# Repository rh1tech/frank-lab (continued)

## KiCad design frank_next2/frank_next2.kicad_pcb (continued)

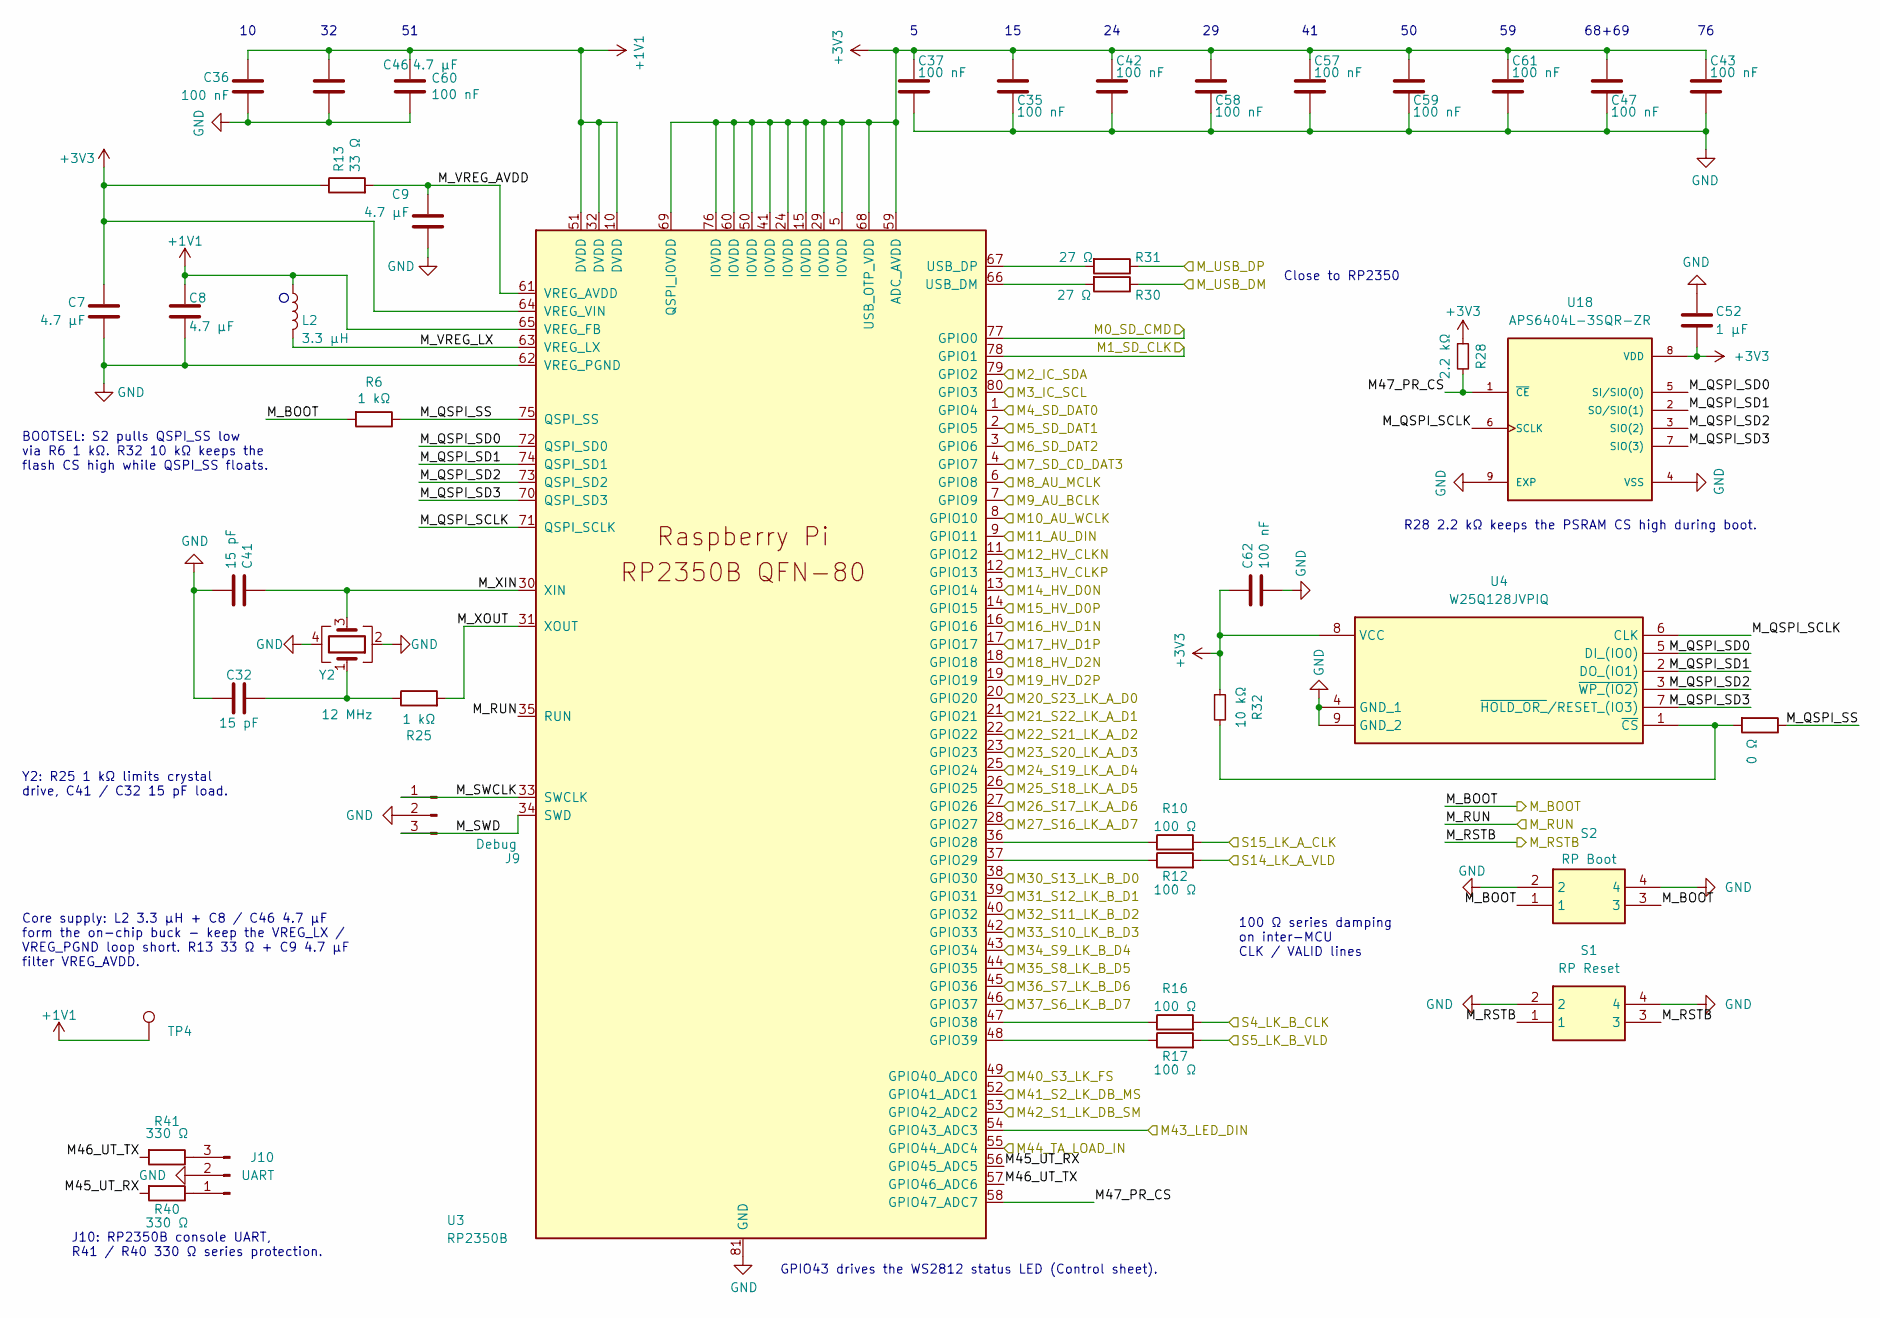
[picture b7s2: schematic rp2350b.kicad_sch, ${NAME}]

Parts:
C7, C8: 4.7 µF 25 V; C_0603_1608Metric_small_pads; LCSC C5360844
C9: 4.7 µF 25 V; C_0603_1608Metric; LCSC C5360844
C32, C41: 15 pF 50 V; C_0603_1608Metric; LCSC C1644
C35, C36, C37, C42, C43, C47, C57, C58, C59, C60, C61: 100 nF 50 V; C_0603_1608Metric_small_pads_Via; LCSC C14663
C46: 4.7 µF 25 V; C_0603_1608Metric_small_pads_Via; LCSC C5360844
C52: 1 µF 50 V; C_0603_1608Metric; LCSC C5199872
C62: 100 nF 50 V; C_0603_1608Metric_small_pads_Via_GND; LCSC C14663
J9: Debug; JST_SH_1x03_P1.00mm_Vertical; LCSC C160389
J10: UART; JST_SH_1x03_P1.00mm_Vertical; LCSC C160389
L2: 3.3 µH; L_AOTA-B201610_2.0x1.6mm; LCSC C42411119
R6, R25: 1 kΩ; R_0603_1608Metric; LCSC C21190
R10, R12, R16, R17: 100 Ω; R_0603_1608Metric; LCSC C22775
R11: 0 Ω; R_0603_1608Metric; LCSC C21189
R13: 33 Ω; R_0603_1608Metric_small_pads; LCSC C23140
R28: 2.2 kΩ; R_0603_1608Metric; LCSC C4190
R30, R31: 27 Ω; R_0603_1608Metric; LCSC C25190
R32: 10 kΩ; R_0603_1608Metric_small_pads_Via; LCSC C2906982
R40, R41: 330 Ω; R_0603_1608Metric; LCSC C23138
S1: RP Reset; Button_SMD_3x4x2mm; Mouser Part Number 611-KMR221G-LFS; LCSC C55200587
S2: RP Boot; Button_SMD_3x4x2mm; Mouser Part Number 611-KMR221G-LFS; LCSC C55200587
TP4: +1V1; TestPoint_Pad_D1.0mm
U3: RP2350B; RP2350-QFN-80_10x10_P0.4mm; LCSC C42415655
U4: W25Q128JVPIQ; WSON-8-1EP_6x5mm_P1.27mm_EP3.45x4.35mm; Mouser Part Number 454-W25Q128JVPIQ; LCSC C190862
U18: APS6404L-3SQR-ZR; PSON50P200X300X50-9N; PARTREV 2.3; LCSC C3040877
Y2: 12 MHz; Crystal_SMD_3225-4Pin_3.2x2.5mm; LCSC C20625731

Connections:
+1V1: C8.1, C36.1, C46.1, C60.1, L2.1, TP4.1 (1_1), U3.10 (DVDD), U3.32 (DVDD), U3.51 (DVDD), U3.65 (VREG_FB)
+3V3: C7.1, C35.1, C37.1, C42.1, C43.1, C47.1, C52.1, C57.1, C58.1, C59.1, C61.1, C62.1, R13.1, R28.1, R32.1, U3.5 (IOVDD), U3.15 (IOVDD), U3.24 (IOVDD), U3.29 (IOVDD), U3.41 (IOVDD), U3.50 (IOVDD), U3.59 (ADC_AVDD), U3.60 (IOVDD), U3.64 (VREG_VIN), U3.68 (USB_OTP_VDD), U3.69 (QSPI_IOVDD), U3.76 (IOVDD), U4.8 (VCC), U18.8 (VDD); also elsewhere on the board
/M0_SD_CMD: U3.77 (GPIO0); also elsewhere on the board
/M1_SD_CLK: U3.78 (GPIO1); also elsewhere on the board
/M2_IC_SDA: U3.79 (GPIO2); also elsewhere on the board
/M3_IC_SCL: U3.80 (GPIO3); also elsewhere on the board
/M4_SD_DAT0: U3.1 (GPIO4); also elsewhere on the board
/M5_SD_DAT1: U3.2 (GPIO5); also elsewhere on the board
/M6_SD_DAT2: U3.3 (GPIO6); also elsewhere on the board
/M7_SD_CD_DAT3: U3.4 (GPIO7); also elsewhere on the board
/M8_AU_MCLK: U3.6 (GPIO8); also elsewhere on the board
/M9_AU_BCLK: U3.7 (GPIO9); also elsewhere on the board
/M10_AU_WCLK: U3.8 (GPIO10); also elsewhere on the board
/M11_AU_DIN: U3.9 (GPIO11); also elsewhere on the board
/M12_HV_CLKN: U3.11 (GPIO12); also elsewhere on the board
/M13_HV_CLKP: U3.12 (GPIO13); also elsewhere on the board
/M14_HV_D0N: U3.13 (GPIO14); also elsewhere on the board
/M15_HV_D0P: U3.14 (GPIO15); also elsewhere on the board
/M16_HV_D1N: U3.16 (GPIO16); also elsewhere on the board
/M17_HV_D1P: U3.17 (GPIO17); also elsewhere on the board
/M18_HV_D2N: U3.18 (GPIO18); also elsewhere on the board
/M19_HV_D2P: U3.19 (GPIO19); also elsewhere on the board
/M20_S23_LK_A_D0: U3.20 (GPIO20); also elsewhere on the board
/M21_S22_LK_A_D1: U3.21 (GPIO21); also elsewhere on the board
/M22_S21_LK_A_D2: U3.22 (GPIO22); also elsewhere on the board
/M23_S20_LK_A_D3: U3.23 (GPIO23); also elsewhere on the board
/M24_S19_LK_A_D4: U3.25 (GPIO24); also elsewhere on the board
/M25_S18_LK_A_D5: U3.26 (GPIO25); also elsewhere on the board
/M26_S17_LK_A_D6: U3.27 (GPIO26); also elsewhere on the board
/M27_S16_LK_A_D7: U3.28 (GPIO27); also elsewhere on the board
/M30_S13_LK_B_D0: U3.38 (GPIO30); also elsewhere on the board
/M31_S12_LK_B_D1: U3.39 (GPIO31); also elsewhere on the board
/M32_S11_LK_B_D2: U3.40 (GPIO32); also elsewhere on the board
/M33_S10_LK_B_D3: U3.42 (GPIO33); also elsewhere on the board
/M34_S9_LK_B_D4: U3.43 (GPIO34); also elsewhere on the board
/M35_S8_LK_B_D5: U3.44 (GPIO35); also elsewhere on the board
/M36_S7_LK_B_D6: U3.45 (GPIO36); also elsewhere on the board
/M37_S6_LK_B_D7: U3.46 (GPIO37); also elsewhere on the board
/M40_S3_LK_FS: U3.49 (GPIO40_ADC0); also elsewhere on the board
/M41_S2_LK_DB_MS: U3.52 (GPIO41_ADC1); also elsewhere on the board
/M42_S1_LK_DB_SM: U3.53 (GPIO42_ADC2); also elsewhere on the board
/M43_LED_DIN: U3.54 (GPIO43_ADC3); also elsewhere on the board
/M_BOOT: R6.2, S2.1, S2.3; also elsewhere on the board
/M_RSTB: S1.1, S1.3; also elsewhere on the board
/M_RUN: U3.35 (RUN); also elsewhere on the board
/RP2350B/M44_TA_LOAD_IN: U3.55 (GPIO44_ADC4); also elsewhere on the board
/RP2350B/M45_UT_RX: R40.2, U3.56 (GPIO45_ADC5)
/RP2350B/M46_UT_TX: R41.2, U3.57 (GPIO46_ADC6)
/RP2350B/M47_PR_CS: R28.2, U3.58 (GPIO47_ADC7), U18.1 (~CE)
/RP2350B/M_QSPI_SCLK: U3.71 (QSPI_SCLK), U4.6 (CLK), U18.6 (SCLK)
/RP2350B/M_QSPI_SD0: U3.72 (QSPI_SD0), U4.5 (DI_(IO0)), U18.5 (SI/SIO(0))
/RP2350B/M_QSPI_SD1: U3.74 (QSPI_SD1), U4.2 (DO_(IO1)), U18.2 (SO/SIO(1))
/RP2350B/M_QSPI_SD2: U3.73 (QSPI_SD2), U4.3 (~WP_(IO2)), U18.3 (SIO(2))
/RP2350B/M_QSPI_SD3: U3.70 (QSPI_SD3), U4.7 (~HOLD_OR_/RESET_(IO3)), U18.7 (SIO(3))
/RP2350B/M_QSPI_SS: R6.1, R11.1, U3.75 (QSPI_SS)
/RP2350B/M_SWCLK: J9.1, U3.33 (SWCLK)
/RP2350B/M_SWD: J9.3, U3.34 (SWD)
/RP2350B/M_USB_DM: R30.1; also elsewhere on the board
/RP2350B/M_USB_DP: R31.1; also elsewhere on the board
/RP2350B/M_VREG_AVDD: C9.1, R13.2, U3.61 (VREG_AVDD)
/RP2350B/M_VREG_LX: L2.2, U3.63 (VREG_LX)
/RP2350B/M_XIN: C41.1, U3.30 (XIN), Y2.3
/RP2350B/M_XOUT: R25.2, U3.31 (XOUT)
/S4_LK_B_CLK: R16.2; also elsewhere on the board
/S5_LK_B_VLD: R17.2; also elsewhere on the board
/S14_LK_A_VLD: R12.2; also elsewhere on the board
/S15_LK_A_CLK: R10.2; also elsewhere on the board
GND: C7.2, C8.2, C9.2, C32.2, C35.2, C36.2, C37.2, C41.2, C42.2, C43.2, C46.2, C47.2, C52.2, C57.2, C58.2, C59.2, C60.2, C61.2, C62.2, J9.2, J10.2, S1.2, S1.4, S2.2, S2.4, U3.62 (VREG_PGND), U3.81 (GND), U4.4 (GND_1), U4.9 (GND_2), U18.4 (VSS), U18.9 (EXP), Y2.2, Y2.4; also elsewhere on the board
unnamed: C32.1, R25.1, Y2.1
unnamed: J10.1, R40.1
unnamed: J10.3, R41.1
unnamed: R10.1, U3.36 (GPIO28)
unnamed: R12.1, U3.37 (GPIO29)
unnamed: R16.1, U3.47 (GPIO38)
unnamed: R17.1, U3.48 (GPIO39)
unnamed: R30.2, U3.66 (USB_DM)
unnamed: R31.2, U3.67 (USB_DP)
unnamed: R11.2, R32.2, U4.1 (~CS)

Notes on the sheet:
J10: RP2350B console UART, R41 / R40 330 Ω series protection.
BOOTSEL: S2 pulls QSPI_SS low via R6 1 kΩ. R32 10 kΩ keeps the flash CS high while QSPI_SS floats.
100 Ω series damping on inter-MCU CLK / VALID lines
Core supply: L2 3.3 µH + C8 / C46 4.7 µF form the on-chip buck - keep the VREG_LX / VREG_PGND loop short. R13 33 Ω + C9 4.7 µF filter VREG_AVDD.
GPIO43 drives the WS2812 status LED (Control sheet).
Close to RP2350
R28 2.2 kΩ keeps the PSRAM CS high during boot.
68+69
Y2: R25 1 kΩ limits crystal drive, C41 / C32 15 pF load.

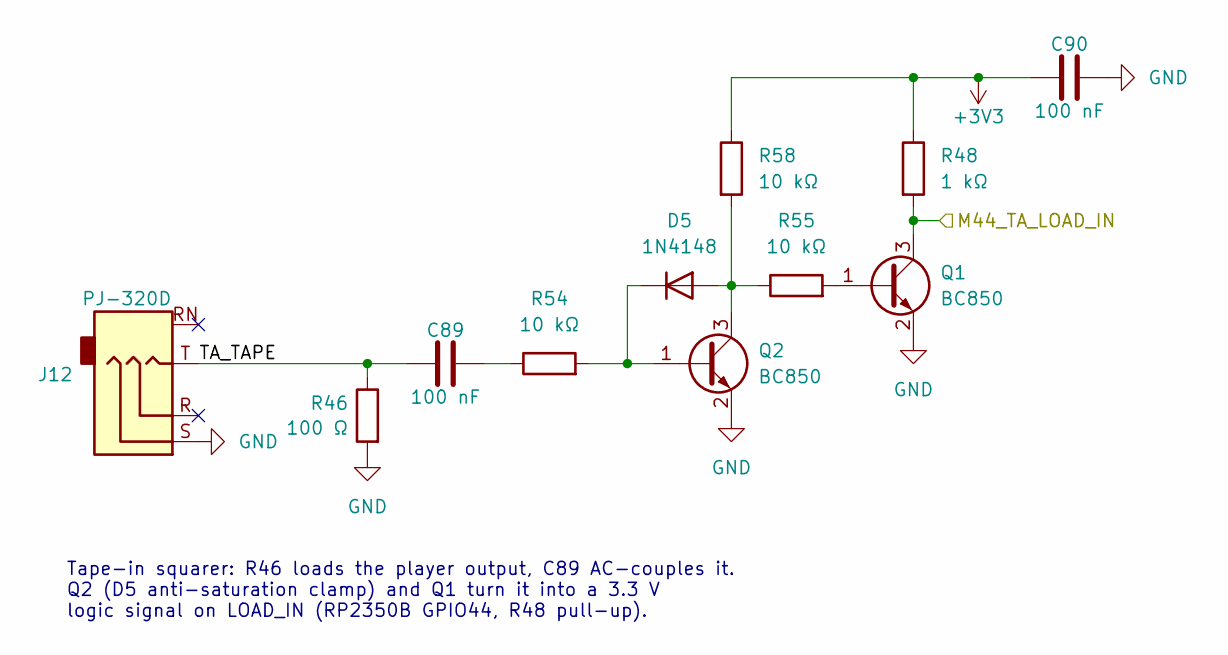
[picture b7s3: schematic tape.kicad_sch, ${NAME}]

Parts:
C89: 100 nF 50 V; C_0603_1608Metric; LCSC C14663
C90: 100 nF 50 V; C_0603_1608Metric_small_pads_Via_GND; LCSC C14663
D5: 1N4148; D_SOD-323; LCSC C2128
J12: PJ-320D; AudioJack_3.5mm_PJ320D_TapeIn; LCSC C431535
Q1, Q2: BC850; SOT-23; LCSC C503377
R46: 100 Ω; R_0603_1608Metric; LCSC C22775
R48: 1 kΩ; R_0603_1608Metric_small_pads_Via; LCSC C21190
R54, R55: 10 kΩ; R_0603_1608Metric; LCSC C2906982
R58: 10 kΩ; R_0603_1608Metric_small_pads_Via; LCSC C2906982

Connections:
+3V3: C90.1, R48.1, R58.1; also elsewhere on the board
/RP2350B/M44_TA_LOAD_IN: Q1.3 (C), R48.2; also elsewhere on the board
/Tape/TA_TAPE: C89.1, J12.T, R46.1
GND: C90.2, J12.S, Q1.2 (E), Q2.2 (E), R46.2; also elsewhere on the board
unnamed: C89.2, R54.1
unnamed: D5.2 (A), Q2.3 (C), R55.1, R58.2
unnamed: D5.1 (K), Q2.1 (B), R54.2
unnamed: Q1.1 (B), R55.2

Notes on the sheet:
Tape-in squarer: R46 loads the player output, C89 AC-couples it. Q2 (D5 anti-saturation clamp) and Q1 turn it into a 3.3 V logic signal on LOAD_IN (RP2350B GPIO44, R48 pull-up).

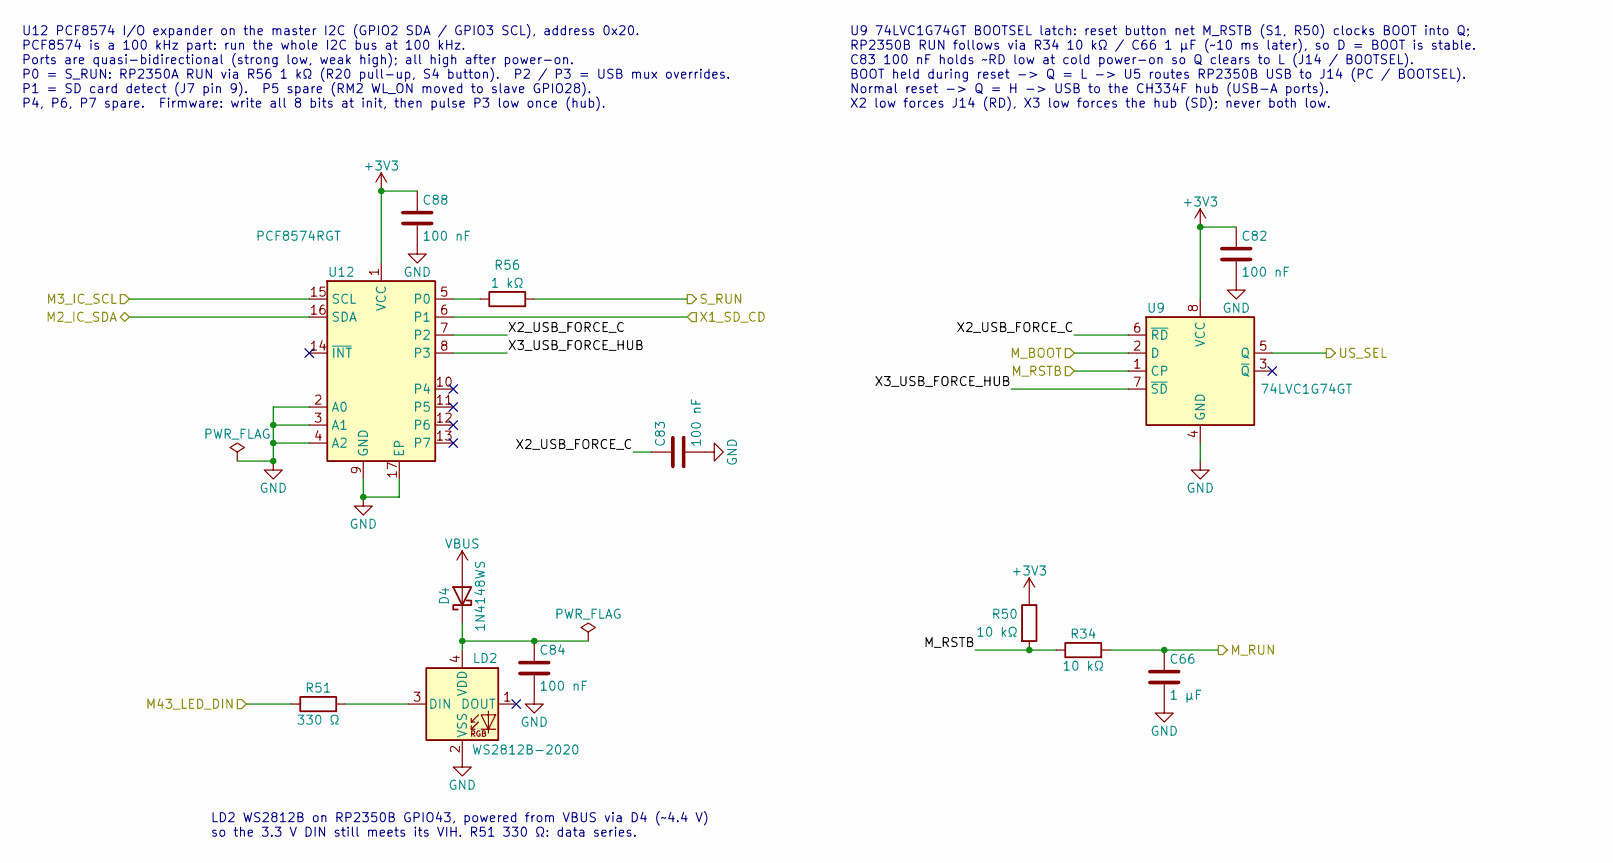
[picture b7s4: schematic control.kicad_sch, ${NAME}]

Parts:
C66: 1 µF 50 V; C_0603_1608Metric; LCSC C5199872
C82, C88: 100 nF 50 V; C_0603_1608Metric_small_pads_Via_GND; LCSC C14663
C83, C84: 100 nF 50 V; C_0603_1608Metric; LCSC C14663
D4: 1N4148WS; D_SOD-323; LCSC C2128
LD2: WS2812B-2020; LED_WS2812B-2020_PLCC4_2.0x2.0mm; LCSC C965555
R34: 10 kΩ; R_0603_1608Metric; LCSC C2906982
R50: 10 kΩ; R_0603_1608Metric_small_pads_Via; LCSC C2906982
R51: 330 Ω; R_0603_1608Metric; LCSC C23138
R56: 1 kΩ; R_0603_1608Metric; LCSC C21190
U9: 74LVC1G74GT; Nexperia_XSON-8_SOT833-1_1x1.95mm_P0.5mm; LCSC C548415
U12: PCF8574RGT; VQFN-16-1EP_3x3mm_P0.5mm_EP1.68x1.68mm; LCSC C2652270

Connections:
+3V3: C82.1, C88.1, R50.1, U9.8 (VCC), U12.1 (VCC); also elsewhere on the board
/Control/X2_USB_FORCE_C: C83.1, U9.6 (~RD), U12.7 (P2)
/Control/X3_USB_FORCE_HUB: U9.7 (~SD), U12.8 (P3)
/M2_IC_SDA: U12.16 (SDA); also elsewhere on the board
/M3_IC_SCL: U12.15 (SCL); also elsewhere on the board
/M43_LED_DIN: R51.1; also elsewhere on the board
/M_BOOT: U9.2 (D); also elsewhere on the board
/M_RSTB: R34.1, R50.2, U9.1 (CP); also elsewhere on the board
/M_RUN: C66.1, R34.2; also elsewhere on the board
/S_RUN: R56.2; also elsewhere on the board
/US_SEL: U9.5 (Q); also elsewhere on the board
/X1_SD_CD: U12.6 (P1); also elsewhere on the board
GND: C66.2, C82.2, C83.2, C84.2, C88.2, LD2.2 (VSS), U9.4 (GND), U12.2 (A0), U12.3 (A1), U12.4 (A2), U12.9 (GND), U12.17 (EP); also elsewhere on the board
unnamed: C84.1, D4.1 (K), LD2.4 (VDD)
unnamed: LD2.3 (DIN), R51.2
unnamed: R56.1, U12.5 (P0)
VBUS: D4.2 (A); also elsewhere on the board

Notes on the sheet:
U9 74LVC1G74GT BOOTSEL latch: reset button net M_RSTB (S1, R50) clocks BOOT into Q; RP2350B RUN follows via R34 10 kΩ / C66 1 µF (~10 ms later), so D = BOOT is stable. C83 100 nF holds ~RD low at cold power-on so Q clears to L (J14 / BOOTSEL). BOOT held during reset -> Q = L -> U5 routes RP2350B US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
LD2 WS2812B on RP2350B GPIO43, powered from VBUS via D4 (~4.4 V) so the 3.3 V DIN still meets its VIH. R51 330 Ω: data series.
U12 PCF8574 I/O expander on the master I2C (GPIO2 SDA / GPIO3 SCL), address 0x20. PCF8574 is a 100 kHz part: run the whole I2C bus at 100 kHz. Ports are quasi-bidirectional (strong low, weak high); all high after power-on. P0 = S_RUN: RP2350A RUN via R56 1 kΩ (R20 pull-up, S4 button). P2 / P3 = USB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

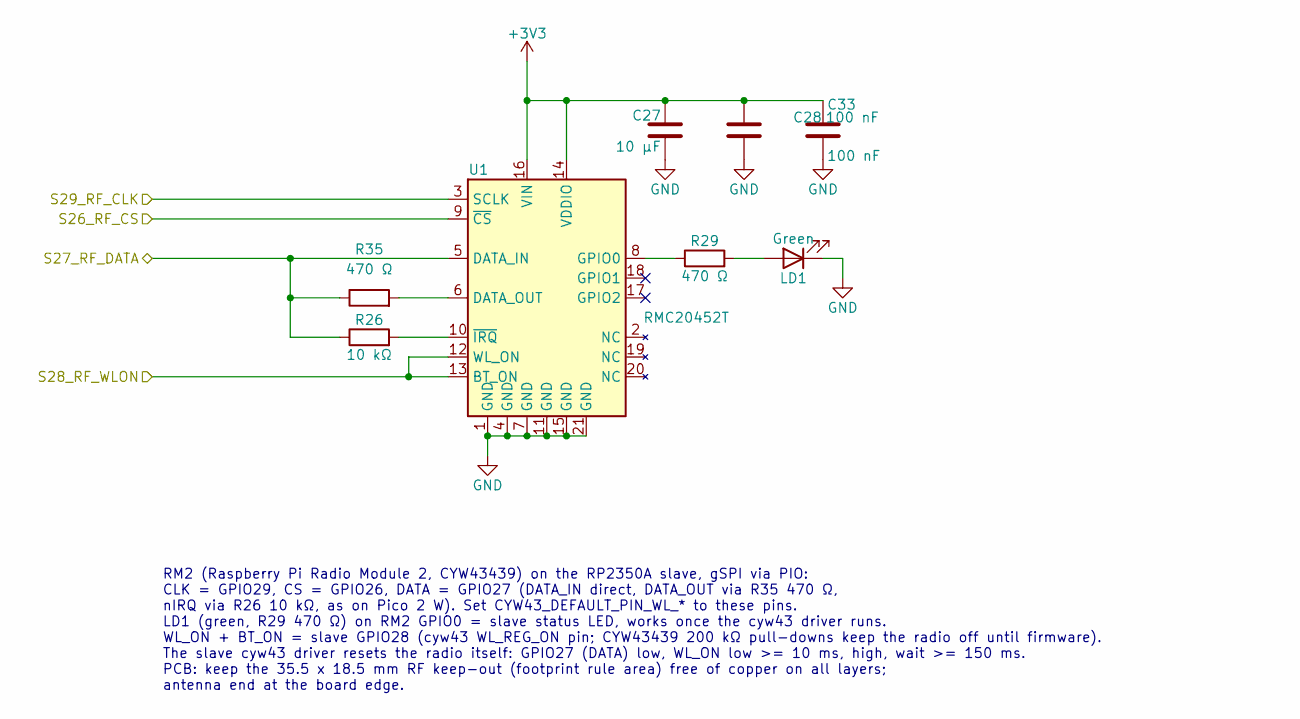
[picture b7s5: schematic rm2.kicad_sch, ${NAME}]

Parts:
C27: 10 µF 25 V; C_0603_1608Metric_small_pads_Via_GND; LCSC C96446
C28, C33: 100 nF 50 V; C_0603_1608Metric_small_pads_Via_GND; LCSC C14663
LD1: Green; LED_0603_1608Metric; LCSC C965804
R26: 10 kΩ; R_0603_1608Metric; LCSC C2906982
R29, R35: 470 Ω; R_0603_1608Metric; LCSC C23179
U1: RMC20452T; RaspberryPi_RM2

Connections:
+3V3: C27.1, C28.1, C33.1, U1.14 (VDDIO), U1.16 (VIN); also elsewhere on the board
/S26_RF_CS: U1.9 (~CS); also elsewhere on the board
/S27_RF_DATA: R26.1, R35.1, U1.5 (DATA_IN); also elsewhere on the board
/S28_RF_WLON: U1.12 (WL_ON), U1.13 (BT_ON); also elsewhere on the board
/S29_RF_CLK: U1.3 (SCLK); also elsewhere on the board
GND: C27.2, C28.2, C33.2, LD1.1 (K), U1.1 (GND), U1.4 (GND), U1.7 (GND), U1.11 (GND), U1.15 (GND), U1.21 (GND); also elsewhere on the board
unnamed: LD1.2 (A), R29.2
unnamed: R35.2, U1.6 (DATA_OUT)
unnamed: R29.1, U1.8 (GPIO0)
unnamed: R26.2, U1.10 (~IRQ)

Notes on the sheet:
RM2 (Raspberry Pi Radio Module 2, CYW43439) on the RP2350A slave, gSPI via PIO: CLK = GPIO29, CS = GPIO26, DATA = GPIO27 (DATA_IN direct, DATA_OUT via R35 470 Ω, nIRQ via R26 10 kΩ, as on Pico 2 W). Set CYW43_DEFAULT_PIN_WL_* to these pins. LD1 (green, R29 470 Ω) on RM2 GPIO0 = slave status LED, wo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

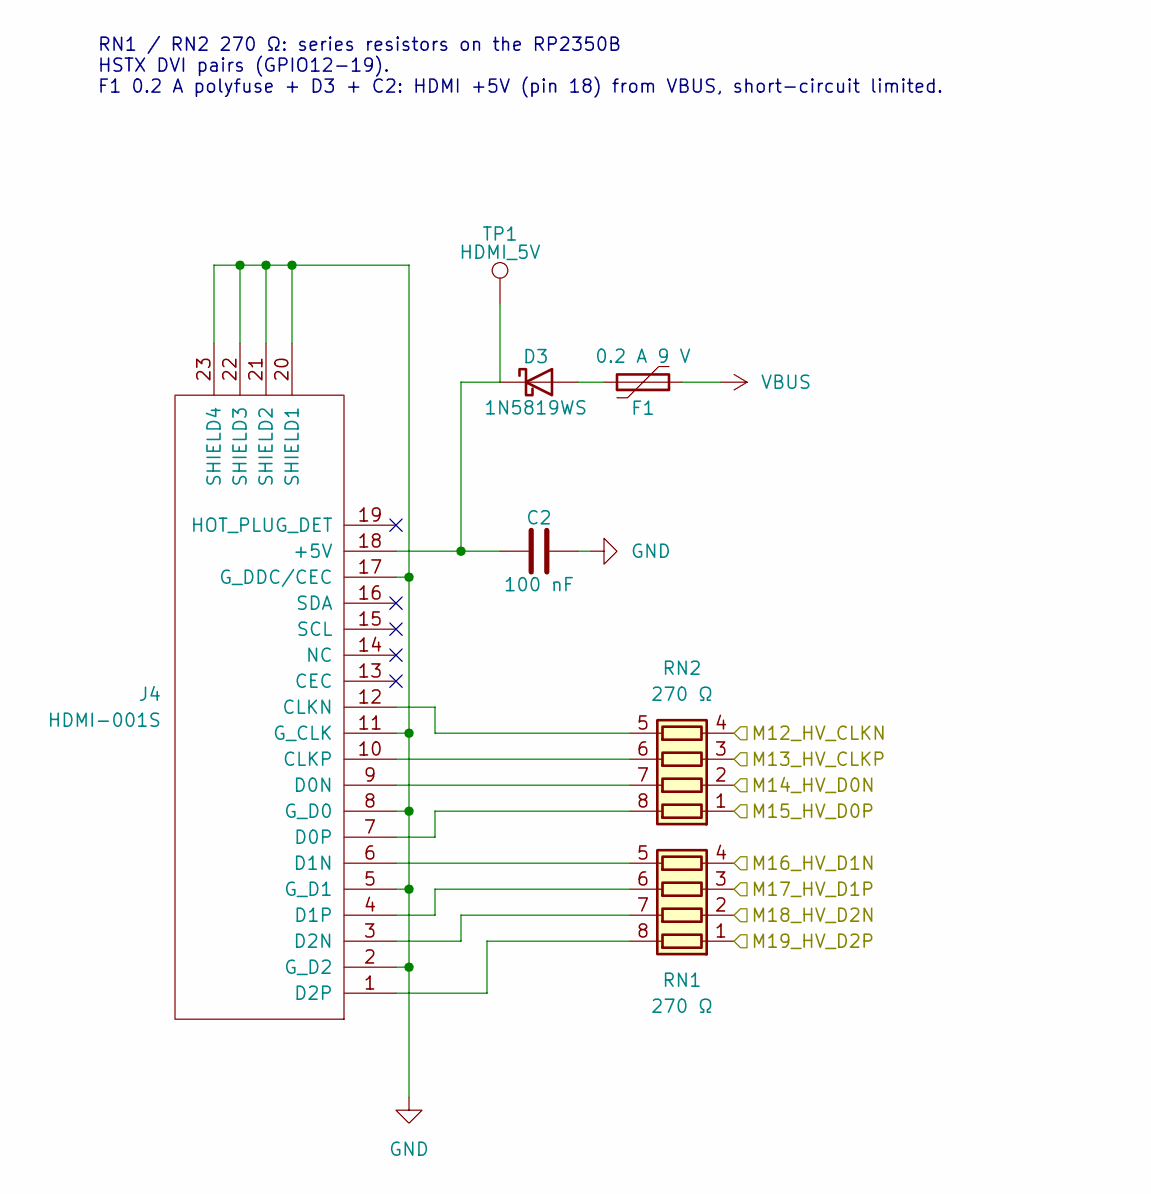
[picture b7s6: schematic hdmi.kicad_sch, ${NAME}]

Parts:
C2: 100 nF 50 V; C_0603_1608Metric; LCSC C14663
D3: 1N5819WS; D_SOD-323; LCSC C191023
F1: 0.2 A 9 V; Fuse_0603_1608Metric; LCSC C20785
J4: HDMI-001S; HDMI_Female; LCSC C720616
RN1, RN2: 270 Ω; R_Array_4x0603; LCSC C1731063
TP1: HDMI_5V; TestPoint_Pad_D1.0mm

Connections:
/M12_HV_CLKN: RN2.4 (R4.1); also elsewhere on the board
/M13_HV_CLKP: RN2.3 (R3.1); also elsewhere on the board
/M14_HV_D0N: RN2.2 (R2.1); also elsewhere on the board
/M15_HV_D0P: RN2.1 (R1.1); also elsewhere on the board
/M16_HV_D1N: RN1.4 (R4.1); also elsewhere on the board
/M17_HV_D1P: RN1.3 (R3.1); also elsewhere on the board
/M18_HV_D2N: RN1.2 (R2.1); also elsewhere on the board
/M19_HV_D2P: RN1.1 (R1.1); also elsewhere on the board
GND: C2.2, J4.2 (G_D2), J4.5 (G_D1), J4.8 (G_D0), J4.11 (G_CLK), J4.17 (G_DDC/CEC), J4.20 (SHIELD1), J4.21 (SHIELD2), J4.22 (SHIELD3), J4.23 (SHIELD4); also elsewhere on the board
unnamed: D3.2 (A), F1.1
unnamed: C2.1, D3.1 (K), J4.18 (+5V), TP1.1 (1_1)
unnamed: J4.12 (CLKN), RN2.5 (R4.2)
unnamed: J4.10 (CLKP), RN2.6 (R3.2)
unnamed: J4.9 (D0N), RN2.7 (R2.2)
unnamed: J4.7 (D0P), RN2.8 (R1.2)
unnamed: J4.6 (D1N), RN1.5 (R4.2)
unnamed: J4.4 (D1P), RN1.6 (R3.2)
unnamed: J4.3 (D2N), RN1.7 (R2.2)
unnamed: J4.1 (D2P), RN1.8 (R1.2)
VBUS: F1.2; also elsewhere on the board

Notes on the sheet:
RN1 / RN2 270 Ω: series resistors on the RP2350B HSTX DVI pairs (GPIO12-19). F1 0.2 A polyfuse + D3 + C2: HDMI +5V (pin 18) from VBUS, short-circuit limited.

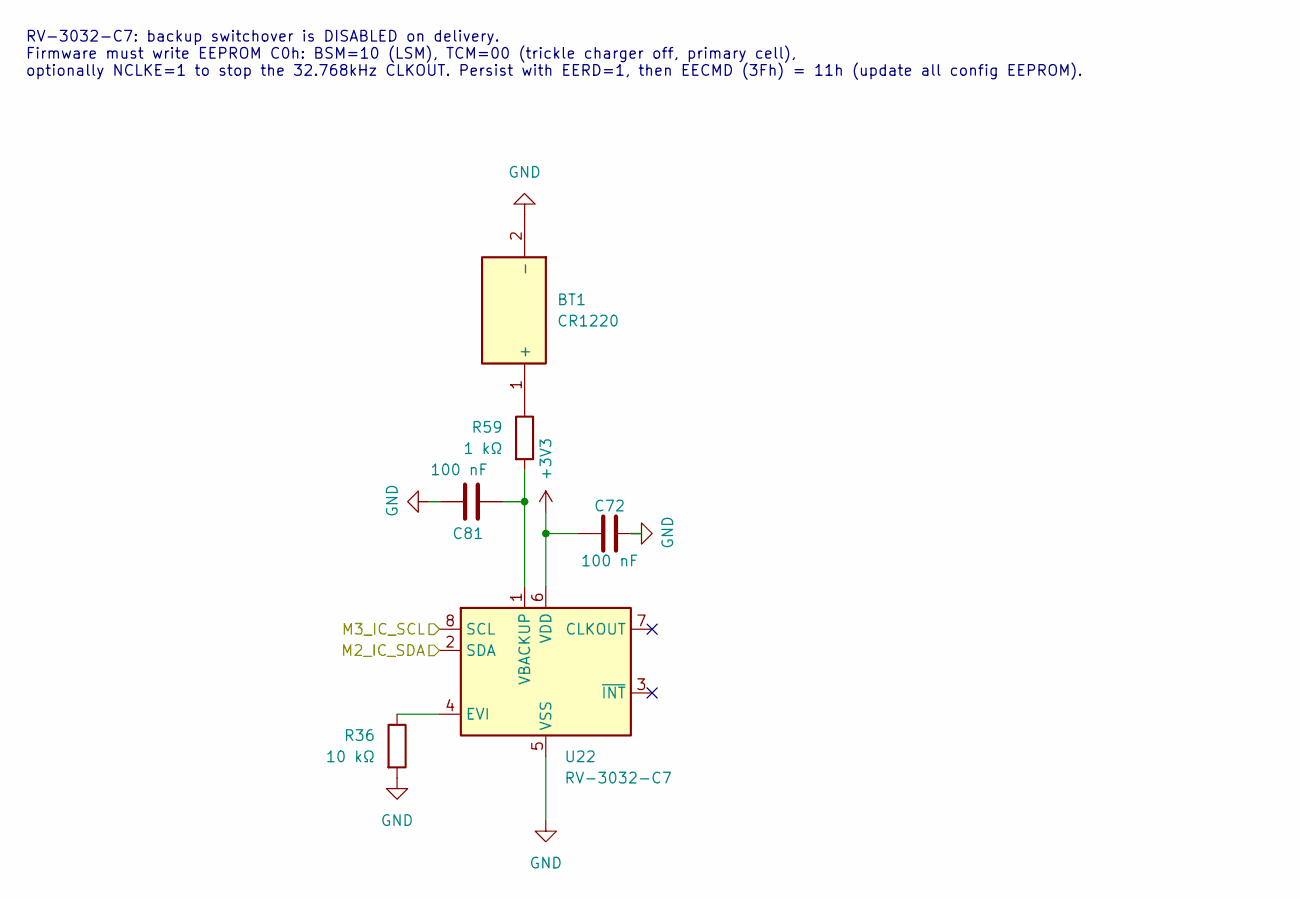
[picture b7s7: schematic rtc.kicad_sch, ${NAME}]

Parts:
BT1: CR1220; Battery_CR1220_MYOUNG_BS-12-B3AA003; Manufacturer_Part_Number BS-12-B3AA003; LCSC C964723
C72: 100 nF 50 V; C_0603_1608Metric_small_pads_Via_GND; LCSC C14663
C81: 100 nF 50 V; C_0603_1608Metric; LCSC C14663
R36: 10 kΩ; R_0603_1608Metric; LCSC C2906982
R59: 1 kΩ; R_0603_1608Metric; LCSC C21190
U22: RV-3032-C7; LCSC C5127802

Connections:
+3V3: C72.1, U22.6 (VDD); also elsewhere on the board
/M2_IC_SDA: U22.2 (SDA); also elsewhere on the board
/M3_IC_SCL: U22.8 (SCL); also elsewhere on the board
GND: BT1.2 (-), C72.2, C81.1, R36.2, U22.5 (VSS); also elsewhere on the board
unnamed: BT1.1 (+), R59.1
unnamed: R36.1, U22.4 (EVI)
unnamed: C81.2, R59.2, U22.1 (VBACKUP)

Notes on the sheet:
RV-3032-C7: backup switchover is DISABLED on delivery. Firmware must write EEPROM C0h: BSM=10 (LSM), TCM=00 (trickle charger off, primary cell), optionally NCLKE=1 to stop the 32.768kHz CLKOUT. Persist with EERD=1, then EECMD (3Fh) = 11h (update all config EEPROM).

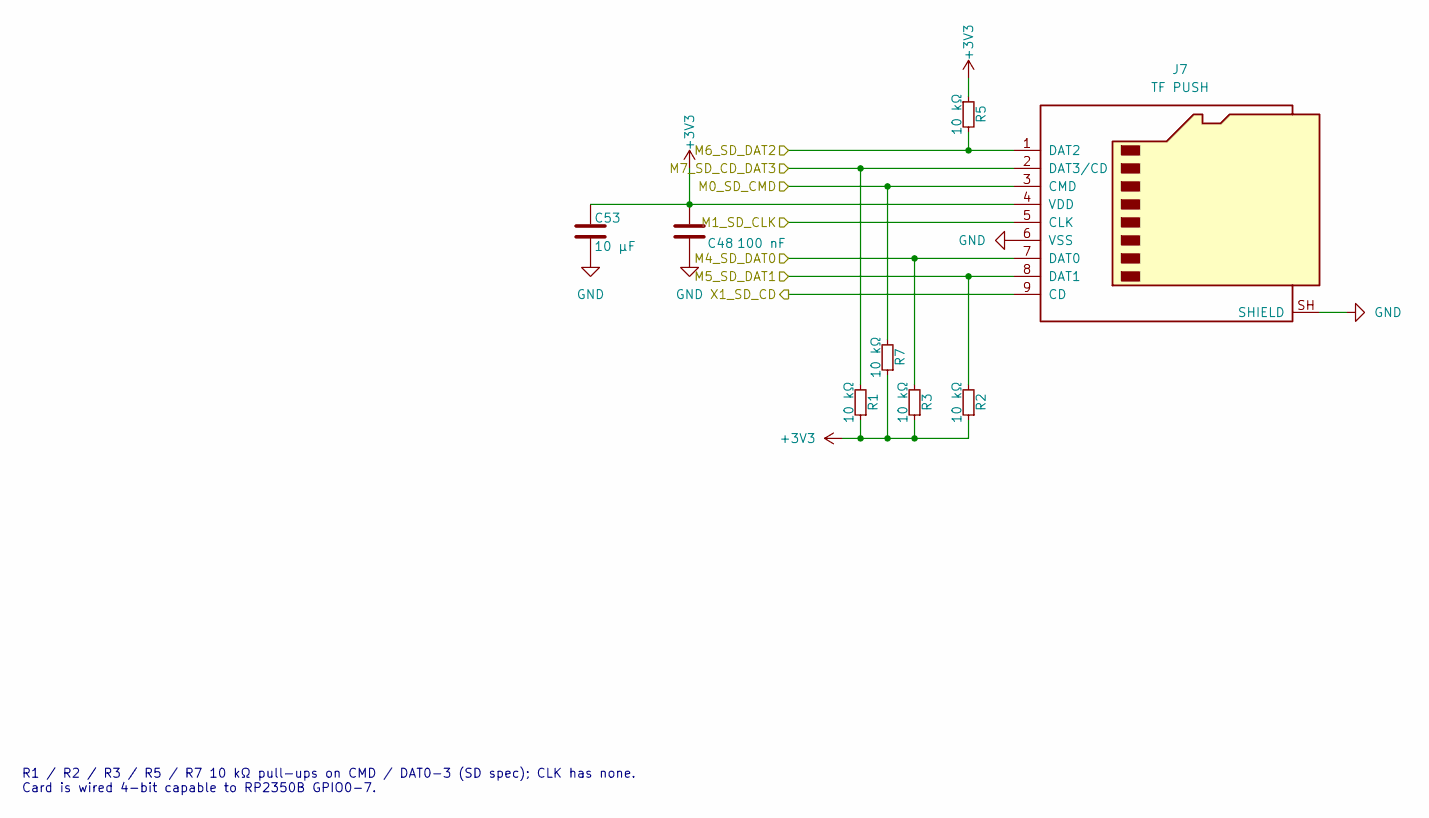
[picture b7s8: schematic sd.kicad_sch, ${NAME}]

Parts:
C48: 100 nF 50 V; C_0603_1608Metric_small_pads_Via_GND; LCSC C14663
C53: 10 µF 25 V; C_0603_1608Metric_small_pads_Via_GND; LCSC C96446
J7: TF PUSH; MicroSD_SMD_Long; LCSC C393941
R1, R2, R3, R5, R7: 10 kΩ; R_0603_1608Metric_small_pads_Via; LCSC C2906982

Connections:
+3V3: C48.1, C53.1, J7.4 (VDD), R1.1, R2.1, R3.1, R5.1, R7.1; also elsewhere on the board
/M0_SD_CMD: J7.3 (CMD), R7.2; also elsewhere on the board
/M1_SD_CLK: J7.5 (CLK); also elsewhere on the board
/M4_SD_DAT0: J7.7 (DAT0), R3.2; also elsewhere on the board
/M5_SD_DAT1: J7.8 (DAT1), R2.2; also elsewhere on the board
/M6_SD_DAT2: J7.1 (DAT2), R5.2; also elsewhere on the board
/M7_SD_CD_DAT3: J7.2 (DAT3/CD), R1.2; also elsewhere on the board
/X1_SD_CD: J7.9 (CD); also elsewhere on the board
GND: C48.2, C53.2, J7.6 (VSS), J7.SH (SHIELD); also elsewhere on the board

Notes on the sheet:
R1 / R2 / R3 / R5 / R7 10 kΩ pull-ups on CMD / DAT0-3 (SD spec); CLK has none. Card is wired 4-bit capable to RP2350B GPIO0-7.

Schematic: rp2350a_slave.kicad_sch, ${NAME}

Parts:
C4: 4.7 µF 25 V; C_0603_1608Metric; LCSC C5360844
C5, C6: 4.7 µF 25 V; C_0603_1608Metric_small_pads; LCSC C5360844
C34, C38, C39, C40, C44, C50, C54, C55, C56: 100 nF 50 V; C_0603_1608Metric_small_pads_Via; LCSC C14663
C45: 4.7 µF 25 V; C_0603_1608Metric_small_pads_Via; LCSC C5360844
C49: 100 nF 50 V; C_0603_1608Metric; LCSC C14663
C51, C65: 15 pF 50 V; C_0603_1608Metric; LCSC C1644
C63: 1 µF 50 V; C_0603_1608Metric_small_pads_Via_GND; LCSC C5199872
J5: Debug; JST_SH_1x03_P1.00mm_Vertical; LCSC C160389
J6: UART; JST_SH_1x03_P1.00mm_Vertical; LCSC C160389
L1: 3.3 µH; L_AOTA-B201610_2.0x1.6mm; LCSC C42411119
R4: 33 Ω; R_0603_1608Metric_small_pads; LCSC C23140
R8, R9: 27 Ω; R_0603_1608Metric; LCSC C25190
R22, R27: 1 kΩ; R_0603_1608Metric; LCSC C21190
R23: 10 kΩ; R_0603_1608Metric; LCSC C2906982
R24: 0 Ω; R_0603_1608Metric; LCSC C21189
R33: 2.2 kΩ; R_0603_1608Metric_small_pads_Via; LCSC C4190
S3: RP Boot; Button_SMD_3x4x2mm; Mouser Part Number 611-KMR221G-LFS; LCSC C55200587
S4: RP Reset; Button_SMD_3x4x2mm; Mouser Part Number 611-KMR221G-LFS; LCSC C55200587
TP3: +1V1_A; TestPoint_Pad_D1.0mm
U2: RP2350; QFN-60-1EP_7x7mm_P0.4mm_EP3.4x3.4mm; LCSC C42411118
U19: W25Q128JVPIQ; WSON-8-1EP_6x5mm_P1.27mm_EP3.45x4.35mm; Mouser Part Number 454-W25Q128JVPIQ; LCSC C190862
U20: APS6404L-3SQR-ZR; PSON50P200X300X50-9N; PARTREV 2.3; LCSC C3040877
Y3: 12 MHz; Crystal_SMD_3225-4Pin_3.2x2.5mm; LCSC C20625731

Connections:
+1V1_A: C5.1, C39.1, C45.1, C55.1, L1.1, TP3.1 (1_1), U2.6 (DVDD), U2.23 (DVDD), U2.39 (DVDD), U2.50 (VREG_FB)
+3V3: C6.1, C34.1, C38.1, C40.1, C44.1, C49.1, C50.1, C54.1, C56.1, C63.1, R4.1, R23.1, R33.1, U2.1 (IOVDD), U2.11 (IOVDD), U2.20 (IOVDD), U2.30 (IOVDD), U2.38 (IOVDD), U2.44 (ADC_AVDD), U2.45 (IOVDD), U2.49 (VREG_VIN), U2.53 (USB_OTP_VDD), U2.54 (QSPI_IOVDD), U19.8 (VCC), U20.8 (VDD); also elsewhere on the board
/M20_S23_LK_A_D0: U2.35 (GPIO23); also elsewhere on the board
/M21_S22_LK_A_D1: U2.34 (GPIO22); also elsewhere on the board
/M22_S21_LK_A_D2: U2.33 (GPIO21); also elsewhere on the board
/M23_S20_LK_A_D3: U2.32 (GPIO20); also elsewhere on the board
/M24_S19_LK_A_D4: U2.31 (GPIO19); also elsewhere on the board
/M25_S18_LK_A_D5: U2.29 (GPIO18); also elsewhere on the board
/M26_S17_LK_A_D6: U2.28 (GPIO17); also elsewhere on the board
/M27_S16_LK_A_D7: U2.27 (GPIO16); also elsewhere on the board
/M30_S13_LK_B_D0: U2.17 (GPIO13); also elsewhere on the board
/M31_S12_LK_B_D1: U2.16 (GPIO12); also elsewhere on the board
/M32_S11_LK_B_D2: U2.15 (GPIO11); also elsewhere on the board
/M33_S10_LK_B_D3: U2.14 (GPIO10); also elsewhere on the board
/M34_S9_LK_B_D4: U2.13 (GPIO9); also elsewhere on the board
/M35_S8_LK_B_D5: U2.12 (GPIO8); also elsewhere on the board
/M36_S7_LK_B_D6: U2.10 (GPIO7); also elsewhere on the board
/M37_S6_LK_B_D7: U2.9 (GPIO6); also elsewhere on the board
/M40_S3_LK_FS: U2.5 (GPIO3); also elsewhere on the board
/M41_S2_LK_DB_MS: U2.4 (GPIO2); also elsewhere on the board
/M42_S1_LK_DB_SM: U2.3 (GPIO1); also elsewhere on the board
/RP2350A/S0_PR_CS: R33.2, U2.2 (GPIO0), U20.1 (~CE)
/RP2350A/S24_UT_TX: J6.3, U2.36 (GPIO24)
/RP2350A/S25_UT_RX: J6.1, U2.37 (GPIO25)
/RP2350A/S_BOOT: R22.2, S3.1, S3.3
/RP2350A/S_QSPI_SCLK: U2.56 (QSPI_SCLK), U19.6 (CLK), U20.6 (SCLK)
/RP2350A/S_QSPI_SD0: U2.57 (QSPI_SD0), U19.5 (DI_(IO0)), U20.5 (SI/SIO(0))
/RP2350A/S_QSPI_SD1: U2.59 (QSPI_SD1), U19.2 (DO_(IO1)), U20.2 (SO/SIO(1))
/RP2350A/S_QSPI_SD2: U2.58 (QSPI_SD2), U19.3 (~WP_(IO2)), U20.3 (SIO(2))
/RP2350A/S_QSPI_SD3: U2.55 (QSPI_SD3), U19.7 (~HOLD_OR_/RESET_(IO3)), U20.7 (SIO(3))
/RP2350A/S_QSPI_SS: R22.1, R24.1, U2.60 (QSPI_SS)
/RP2350A/S_SWCLK: J5.1, U2.24 (SWCLK)
/RP2350A/S_SWD: J5.3, U2.25 (SWD)
/RP2350A/S_VREG_AVDD: C4.1, R4.2, U2.46 (VREG_AVDD)
/RP2350A/S_VREG_LX: L1.2, U2.48 (VREG_LX)
/RP2350A/S_XIN: C51.1, U2.21 (XIN), Y3.3
/RP2350A/S_XOUT: R27.2, U2.22 (XOUT)
/S4_LK_B_CLK: U2.7 (GPIO4); also elsewhere on the board
/S5_LK_B_VLD: U2.8 (GPIO5); also elsewhere on the board
/S14_LK_A_VLD: U2.18 (GPIO14); also elsewhere on the board
/S15_LK_A_CLK: U2.19 (GPIO15); also elsewhere on the board
/S26_RF_CS: U2.40 (GPIO26_ADC0); also elsewhere on the board
/S27_RF_DATA: U2.41 (GPIO27_ADC1); also elsewhere on the board
/S28_RF_WLON: U2.42 (GPIO28_ADC2); also elsewhere on the board
/S29_RF_CLK: U2.43 (GPIO29_ADC3); also elsewhere on the board
/S_RUN: S4.1, S4.3, U2.26 (RUN); also elsewhere on the board
/USB/S_USB_DM: R9.1; also elsewhere on the board
/USB/S_USB_DP: R8.1; also elsewhere on the board
GND: C4.2, C5.2, C6.2, C34.2, C38.2, C39.2, C40.2, C44.2, C45.2, C49.2, C50.2, C51.2, C54.2, C55.2, C56.2, C63.2, C65.2, J5.2, J6.2, S3.2, S3.4, S4.2, S4.4, U2.47 (VREG_PGND), U2.61 (GND), U19.4 (GND_1), U19.9 (GND_2), U20.4 (VSS), U20.9 (EXP), Y3.2, Y3.4; also elsewhere on the board
unnamed: C65.1, R27.1, Y3.1
unnamed: R9.2, U2.51 (USB_DM)
unnamed: R8.2, U2.52 (USB_DP)
unnamed: R23.2, R24.2, U19.1 (~CS)

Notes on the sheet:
44+45
Core supply: L1 3.3 µH + C5 / C45 4.7 µF = on-chip buck, keep the loop short. R4 33 Ω + C4 4.7 µF filter VREG_AVDD.
Make sure these are close to RP2350
PSRAM: one APS6404L (U20, 8 MB) on QMI CS1 = GPIO0, R33 2.2 kΩ pull-up. GPIO28 = S28_RF_WLON (RM2 WL_ON + BT_ON).
S3 BOOT: QSPI_SS low via R22 1 kΩ. RUN (S_RUN) = U12 P0 via R56 (Control sheet).
53+54

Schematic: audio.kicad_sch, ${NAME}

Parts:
C11, C67, C70, C71, C75: 100 nF 50 V; C_0603_1608Metric_small_pads_Via_GND; LCSC C14663
C13, C18, C64, C74, C78, C80: 10 µF 25 V; C_0603_1608Metric_small_pads_Via_GND; LCSC C96446
C68: 1 µF 50 V; C_0603_1608Metric_small_pads_Via_GND; LCSC C5199872
C79: 1 µF 50 V; C_0603_1608Metric; LCSC C5199872
C87, C91: 100 µF 10 V; C_1206_3216Metric; LCSC C7432784
J8: Speaker; JST_GH_1x02_P1.25mm; LCSC C114130
J11: PJ-320D; AudioJack_3.5mm_PJ320D_AudioOut; LCSC C431535
L5: 330 Ω@100 MHz 2.5 A; L_0805_2012Metric; LCSC C76819
R14, R15: 4.7 kΩ; R_0603_1608Metric_small_pads_Via; LCSC C23162
R44: 10 kΩ; R_0603_1608Metric_small_pads_Via; LCSC C2906982
TP9: +5V_SPK; TestPoint_Pad_D1.0mm
TP10: +1V8; TestPoint_Pad_D1.0mm
U7: TLV320DAC3100IRHBR; Mouser Part Number 595-V320DAC3100IRHBR; LCSC C179677
U21: XC6206P182MR-G; Mouser Part Number 865-XC6206P182MR-G; LCSC C347373

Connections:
+1V8: C71.1, C80.1, TP10.1 (1_1), U7.3 (DVDD), U21.2 (VOUT)
+3V3: C11.1, C13.1, C18.1, C64.1, C67.1, C68.1, C75.1, R14.1, R15.1, R44.1, U7.2 (IOVDD), U7.17 (AVDD), U7.28 (HPVDD), U21.3 (VIN); also elsewhere on the board
/Audio/+5V_SPK: C70.1, C74.1, C78.1, L5.1, TP9.1 (1_1), U7.21 (SPKVDD_1), U7.24 (SPKVDD_2)
/Audio/AU_SPKM: J8.2, U7.19 (SPKM_1), U7.23 (SPKM_2)
/Audio/AU_SPKP: J8.1, U7.22 (SPKP_1), U7.26 (SPKP_2)
/M2_IC_SDA: R15.2, U7.9 (SDA); also elsewhere on the board
/M3_IC_SCL: R14.2, U7.10 (SCL); also elsewhere on the board
/M8_AU_MCLK: U7.8 (MCLK); also elsewhere on the board
/M9_AU_BCLK: U7.7 (BCLK); also elsewhere on the board
/M10_AU_WCLK: U7.6 (WCLK); also elsewhere on the board
/M11_AU_DIN: U7.5 (DIN); also elsewhere on the board
GND: C11.2, C13.2, C18.2, C64.2, C67.2, C68.2, C70.2, C71.2, C74.2, C75.2, C78.2, C79.2, C80.2, J11.S, U7.1 (IOVSS), U7.16 (AVSS), U7.18 (DVSS), U7.20 (SPKVSS_1), U7.25 (SPKVSS_2), U7.29 (HPVSS), U7.33 (EP), U21.1 (VSS); also elsewhere on the board
unnamed: C87.1, J11.T
unnamed: C91.1, J11.R
unnamed: C87.2, U7.27 (HPL)
unnamed: C91.2, U7.30 (HPR)
unnamed: C79.1, R44.2, U7.31 (~RESET)
VBUS: L5.2; also elsewhere on the board

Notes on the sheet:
U7 TLV320DAC3100, I2C address 0x18 on GPIO2 / GPIO3 (shared with RTC U22 and U12, R14 / R15 4.7 kΩ pull-ups). I2S: MCLK GPIO8, BCLK GPIO9, WCLK GPIO10, DIN GPIO11. DVDD 1.8 V from U21 XC6206 LDO. SPKVDD from VBUS through L5 ferrite; C74 / C78 / C70 at the SPKVDD pins. Headphone HPL / HPR AC-coupled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
